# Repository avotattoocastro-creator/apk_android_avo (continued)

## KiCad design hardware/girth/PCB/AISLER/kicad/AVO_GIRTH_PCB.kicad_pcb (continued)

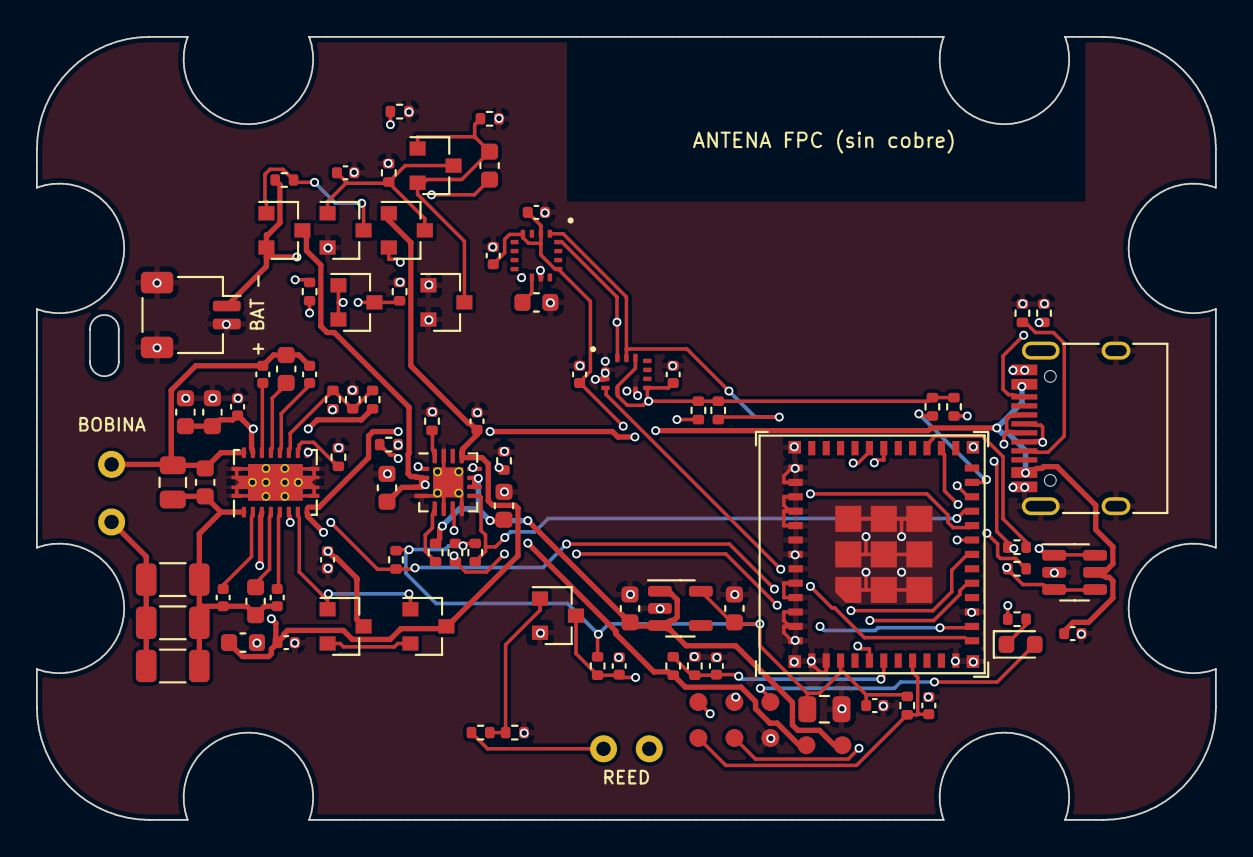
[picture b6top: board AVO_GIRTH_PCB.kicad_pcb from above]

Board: 4 copper layers, 65.5 x 43.5 mm, 98 parts (0 on the bottom side), 55 nets.

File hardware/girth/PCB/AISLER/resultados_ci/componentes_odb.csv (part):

ref,capa,x_mm,y_mm,giro,no_pop,montaje,Value,MPN,Manufacturer,LCSC,paquete
C1,COMP_+_TOP,74.8,-108.4,0.0,False,smt,100n C0G 50V,GRM31C5C1H104JA01L,Murata Electronics,C97946,AVO_C_1206_3216Metric
C2,COMP_+_TOP,74.8,-110.8,0.0,False,smt,100n C0G 50V,GRM31C5C1H104JA01L,Murata Electronics,C97946,AVO_C_1206_3216Metric
C3,COMP_+_TOP,74.8,-113.2,0.0,False,smt,47n C0G 50V,GRM31M5C1H473JA01L,Murata Electronics,C21812,AVO_C_1206_3216Metric
C4,COMP_+_TOP,74.8,-103.0,270.0,False,smt,2n2 C0G 50V,0805CG222J500NT,FH (Guangdong Fenghua Advanced Tech),C51795,AVO_C_0805_2012Metric
C5,COMP_+_TOP,76.6,-103.0,270.0,True,smt,1n C0G 50V,1n C0G 50V,,C1636,AVO_C_0603_1608Metric
C6,COMP_+_TOP,77.6,-109.4,90.0,False,smt,10n 50V,CL05B103KB5NNNC,Samsung Electro-Mechanics,C15195,AVO_C_0402_1005Metric
C7,COMP_+_TOP,79.4,-109.6,90.0,False,smt,470n 25V,CL10B474KA8NNNC,Samsung Electro-Mechanics,C1623,AVO_C_0603_1608Metric
C8,COMP_+_TOP,80.6,-109.4,90.0,False,smt,22n 50V,0402B223K500NT,FH (Guangdong Fenghua Advanced Tech),C1532,AVO_C_0402_1005Metric
C9,COMP_+_TOP,79.8,-97.0,270.0,False,smt,10n 50V,CL05B103KB5NNNC,Samsung Electro-Mechanics,C15195,AVO_C_0402_1005Metric
C10,COMP_+_TOP,81.1,-96.7,270.0,False,smt,470n 25V,CL10B474KA8NNNC,Samsung Electro-Mechanics,C1623,AVO_C_0603_1608Metric
C11,COMP_+_TOP,82.4,-97.0,270.0,False,smt,22n 50V,0402B223K500NT,FH (Guangdong Fenghua Advanced Tech),C1532,AVO_C_0402_1005Metric
C12,COMP_+_TOP,77.0,-99.1,270.0,False,smt,10u 25V,CL10A106MA8NRNC,Samsung Electro-Mechanics,C96446,AVO_C_0603_1608Metric
C13,COMP_+_TOP,75.5,-99.1,270.0,False,smt,10u 25V,CL10A106MA8NRNC,Samsung Electro-Mechanics,C96446,AVO_C_0603_1608Metric
C14,COMP_+_TOP,78.4,-98.8,270.0,False,smt,100n,CL05B104KO5NNNC,Samsung Electro-Mechanics,C1525,AVO_C_0402_1005Metric
C15,COMP_+_TOP,78.7,-111.9,0.0,False,smt,10u 25V,CL10A106MA8NRNC,Samsung Electro-Mechanics,C96446,AVO_C_0603_1608Metric
C16,COMP_+_TOP,81.1,-111.9,0.0,False,smt,100n,CL05B104KO5NNNC,Samsung Electro-Mechanics,C1525,AVO_C_0402_1005Metric
C17,COMP_+_TOP,83.4,-107.3,90.0,False,smt,1u,CL05A105KA5NQNC,Samsung Electro-Mechanics,C52923,AVO_C_0402_1005Metric
C18,COMP_+_TOP,91.7,-99.6,270.0,False,smt,1u,CL05A105KA5NQNC,Samsung Electro-Mechanics,C52923,AVO_C_0402_1005Metric
C19,COMP_+_TOP,93.2,-104.3,270.0,False,smt,10u 25V,CL10A106MA8NRNC,Samsung Electro-Mechanics,C96446,AVO_C_0603_1608Metric
C20,COMP_+_TOP,86.7,-103.3,270.0,False,smt,10u 25V,CL10A106MA8NRNC,Samsung Electro-Mechanics,C96446,AVO_C_0603_1608Metric
C21,COMP_+_TOP,100.2,-110.0,270.0,False,smt,10u 25V,CL10A106MA8NRNC,Samsung Electro-Mechanics,C96446,AVO_C_0603_1608Metric
C22,COMP_+_TOP,106.0,-110.0,270.0,False,smt,10u 25V,CL10A106MA8NRNC,Samsung Electro-Mechanics,C96446,AVO_C_0603_1608Metric
C23,COMP_+_TOP,111.0,-115.6,0.0,False,smt,22u 10V,CL21A226MAQNNNE,Samsung Electro-Mechanics,C45783,AVO_C_0805_2012Metric
C24,COMP_+_TOP,113.8,-115.4,0.0,False,smt,100n,CL05B104KO5NNNC,Samsung Electro-Mechanics,C1525,AVO_C_0402_1005Metric
C25,COMP_+_TOP,116.8,-115.4,270.0,False,smt,1u,CL05A105KA5NQNC,Samsung Electro-Mechanics,C52923,AVO_C_0402_1005Metric
C26,COMP_+_TOP,124.8,-111.4,0.0,False,smt,1u,CL05A105KA5NQNC,Samsung Electro-Mechanics,C52923,AVO_C_0402_1005Metric
C27,COMP_+_TOP,97.4,-97.0,270.0,False,smt,100n,CL05B104KO5NNNC,Samsung Electro-Mechanics,C1525,AVO_C_0402_1005Metric
C28,COMP_+_TOP,102.6,-97.0,270.0,False,smt,100n,CL05B104KO5NNNC,Samsung Electro-Mechanics,C1525,AVO_C_0402_1005Metric
C29,COMP_+_TOP,92.6,-90.4,270.0,False,smt,1u,CL05A105KA5NQNC,Samsung Electro-Mechanics,C52923,AVO_C_0402_1005Metric
C30,COMP_+_TOP,95.0,-93.0,0.0,False,smt,10u 6V3,CL10A106KP8NNNC,Samsung Electro-Mechanics,C19702,AVO_C_0603_1608Metric
C31,COMP_+_TOP,95.0,-88.0,0.0,False,smt,100n,CL05B104KO5NNNC,Samsung Electro-Mechanics,C1525,AVO_C_0402_1005Metric
C33,COMP_+_TOP,99.6,-113.2,270.0,False,smt,10n 50V,CL05B103KB5NNNC,Samsung Electro-Mechanics,C15195,AVO_C_0402_1005Metric
C34,COMP_+_TOP,105.0,-113.2,270.0,False,smt,100n,CL05B104KO5NNNC,Samsung Electro-Mechanics,C1525,AVO_C_0402_1005Metric
C40,COMP_+_TOP,92.4,-85.4,270.0,False,smt,2u2,CL10A225KO8NNNC,Samsung Electro-Mechanics,C23630,AVO_C_0603_1608Metric
C41,COMP_+_TOP,84.4,-85.8,0.0,False,smt,220n,CL05B224KO5NNNC,Samsung Electro-Mechanics,C16772,AVO_C_0402_1005Metric
D1,COMP_+_TOP,121.9,-112.0,0.0,False,smt,LED rojo,KT-0603R,Hubei KENTO Elec,C2286,AVO_LED_0603_1608Metric
D10,COMP_+_TOP,87.8,-89.0,0.0,False,smt,BAV70,BAV70,"Jiangsu Changjing Electronics Technology Co., Ltd.",C68978,AVO_SOT-23
D11,COMP_+_TOP,89.4,-85.4,0.0,False,smt,BAV70,BAV70,"Jiangsu Changjing Electronics Technology Co., Ltd.",C68978,AVO_SOT-23
D12,COMP_+_TOP,85.0,-93.0,0.0,False,smt,BAV70,BAV70,"Jiangsu Changjing Electronics Technology Co., Ltd.",C68978,AVO_SOT-23
D13,COMP_+_TOP,90.0,-93.0,0.0,False,smt,BAV70,BAV70,"Jiangsu Changjing Electronics Technology Co., Ltd.",C68978,AVO_SOT-23
J1,COMP_+_TOP,126.15,-100.0,270.0,False,smt,USB-C 16P,TYPE-C-31-M-12,Korean Hroparts Elec,C165948,AVO_USB_C_Receptacle_HRO_TYPE-C-31-M-12
J2,COMP_+_TOP,75.8,-93.7,90.0,False,smt,BATERÍA 1S,SM02B-SRSS-TB(LF)(SN),JST,C160402,AVO_JST_SH_SM02B-SRSS-TB_1x02-1MP_P1.00mm_Horizontal
L1,COMP_+_TOP,71.4,-105.2,0.0,True,thmt,BOBINA Qi (1),BOBINA Qi (1),,,AVO_WirePad_D1.5_Drill0.8
L2,COMP_+_TOP,71.4,-102.0,0.0,True,thmt,BOBINA Qi (2),BOBINA Qi (2),,,AVO_WirePad_D1.5_Drill0.8
Q1,COMP_+_TOP,84.4,-111.0,0.0,False,smt,AO3401A,AO3401A,Alpha & Omega Semicon,C15127,AVO_SOT-23
Q2,COMP_+_TOP,89.0,-111.0,0.0,False,smt,AO3401A,AO3401A,Alpha & Omega Semicon,C15127,AVO_SOT-23
Q10,COMP_+_TOP,81.0,-89.0,0.0,False,smt,AO3401A,AO3401A,Alpha & Omega Semicon,C15127,AVO_SOT-23
Q11,COMP_+_TOP,84.4,-89.0,0.0,False,smt,AO3400A,AO3400A,Alpha & Omega Semicon,C20917,AVO_SOT-23
Q16,COMP_+_TOP,96.2,-110.4,0.0,False,smt,2N7002,2N7002,"Jiangsu Changjing Electronics Technology Co., Ltd.",C8545,AVO_SOT-23
R1,COMP_+_TOP,83.7,-98.4,270.0,False,smt,330R,0402WGF3300TCE,UNI-ROYAL(Uniroyal Elec),C25104,AVO_R_0402_1005Metric
R2,COMP_+_TOP,84.8,-98.4,270.0,False,smt,200R,0402WGF2000TCE,UNI-ROYAL(Uniroyal Elec),C25087,AVO_R_0402_1005Metric
R3,COMP_+_TOP,85.9,-98.4,270.0,False,smt,20k,0402WGF2002TCE,UNI-ROYAL(Uniroyal Elec),C25765,AVO_R_0402_1005Metric
R4,COMP_+_TOP,87.2,-107.3,270.0,False,smt,100k,0402WGF1003TCE,UNI-ROYAL(Uniroyal Elec),C25741,AVO_R_0402_1005Metric
R6,COMP_+_TOP,89.2,-99.6,270.0,False,smt,3k3,0402WGF3301TCE,UNI-ROYAL(Uniroyal Elec),C25890,AVO_R_0402_1005Metric
R7,COMP_+_TOP,93.2,-101.8,270.0,False,smt,3k3,0402WGF3301TCE,UNI-ROYAL(Uniroyal Elec),C25890,AVO_R_0402_1005Metric
R8,COMP_+_TOP,89.4,-106.9,270.0,False,smt,100k,0402WGF1003TCE,UNI-ROYAL(Uniroyal Elec),C25741,AVO_R_0402_1005Metric
R9,COMP_+_TOP,90.5,-106.9,270.0,False,smt,100k,0402WGF1003TCE,UNI-ROYAL(Uniroyal Elec),C25741,AVO_R_0402_1005Metric
R10,COMP_+_TOP,91.6,-106.9,270.0,False,smt,100k,0402WGF1003TCE,UNI-ROYAL(Uniroyal Elec),C25741,AVO_R_0402_1005Metric
R11,COMP_+_TOP,115.6,-115.4,270.0,False,smt,10k,0402WGF1002TCE,UNI-ROYAL(Uniroyal Elec),C25744,AVO_R_0402_1005Metric
R12,COMP_+_TOP,117.0,-98.8,270.0,False,smt,10k,0402WGF1002TCE,UNI-ROYAL(Uniroyal Elec),C25744,AVO_R_0402_1005Metric
R13,COMP_+_TOP,118.2,-98.8,270.0,False,smt,10k,0402WGF1002TCE,UNI-ROYAL(Uniroyal Elec),C25744,AVO_R_0402_1005Metric
R15,COMP_+_TOP,121.7,-110.6,0.0,False,smt,1k,0402WGF1001TCE,UNI-ROYAL(Uniroyal Elec),C11702,AVO_R_0402_1005Metric
R16,COMP_+_TOP,122.0,-93.6,270.0,False,smt,5k1,0402WGF5101TCE,UNI-ROYAL(Uniroyal Elec),C25905,AVO_R_0402_1005Metric
R17,COMP_+_TOP,123.2,-93.6,270.0,False,smt,5k1,0402WGF5101TCE,UNI-ROYAL(Uniroyal Elec),C25905,AVO_R_0402_1005Metric
R18,COMP_+_TOP,121.7,-106.6,0.0,False,smt,22R,0402WGF220JTCE,UNI-ROYAL(Uniroyal Elec),C25092,AVO_R_0402_1005Metric
R19,COMP_+_TOP,121.7,-107.8,0.0,False,smt,22R,0402WGF220JTCE,UNI-ROYAL(Uniroyal Elec),C25092,AVO_R_0402_1005Metric
R20,COMP_+_TOP,104.0,-99.0,270.0,False,smt,4k7,0402WGF4701TCE,UNI-ROYAL(Uniroyal Elec),C25900,AVO_R_0402_1005Metric
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
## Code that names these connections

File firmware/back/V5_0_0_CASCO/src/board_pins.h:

// AVO CASCO BACK V5 (PROTOTIPO A y REV B: mismos GPIO) — mapa de pines.
// Fuente: hardware/back/V5_CASCO_PROTOTIPO/PCB/fuente/avo_back_v5_pcb.py (diccionario GPIO del módulo U4,
// ESP32-S3-WROOM-1U-N16R8) y la revisión previa a fabricación (claude/AVO_BACK_V5_REVISION_PRE_FABRICACION).
// Los nombres que ya usaba el pecho (PIN_I2C_*, PIN_SD_*, PIN_BOOT_BTN, PIN_PWR_SENSE) se conservan para no tocar
// sus módulos; el resto son nuevos del casco.
#pragma once

#define AVO_CASCO 1

// ---------------------------------------------------------------- I2C: MAX17048 (0x36) + LSM6DSV16X (0x6A)
#define PIN_I2C_SDA 42
#define PIN_I2C_SCL 41
#define I2C_FREQ_HZ 400000
#define I2C_ADDR_MAX17048 0x36
#define I2C_ADDR_LSM6DSV16X 0x6A

// ---------------------------------------------------------------- microSD (SDMMC 4 bits) + interruptor de alimentación
#define PIN_SD_CLK 12
#define PIN_SD_CMD 13
#define PIN_SD_D0 14
#define PIN_SD_D1 15
#define PIN_SD_D2 16
#define PIN_SD_D3 17
#define PIN_SD_PWR_N 21          // Q4 (PMOS): 0 = tarjeta alimentada, 1 = cortada (R40 la deja apagada al arrancar)

// ---------------------------------------------------------------- encendido y entradas
#define PIN_PWR_HOLD 46          // enclavamiento del 3,3 V (pin de arranque: R15 100k a GND). 1 = mantener encendido
#define PIN_TOUCH 11             // salida del TTP223 (activa ALTA mientras se toca). RTC: despierta del sueño profundo
#define PIN_VBUS_DET 18          // 1 = cable del pogo o USB-C conectado (divisor 1k/1k5, RTC)
#define PIN_CHG_PG 38            // BQ24072 PGOOD (colector abierto, activo BAJO): entrada válida
#define PIN_CHG_STAT 39          // BQ24072 CHG (colector abierto, activo BAJO): cargando
#define PIN_BAT_ADC 2            // divisor 1:2 de VBAT (ADC1_CH1); reserva si el MAX17048 no responde
#define PIN_HALL 1               // DRV5032: 0 = casco en la base con imán (RTC)
#define PIN_IMU_INT1 4           // LSM6DSV16X INT1 (RTC)
#define PIN_POGO_AUX 40          // contacto libre del pogo (reservado)

// El pecho leía un botón BOOT (activo BAJO) y la tecla PWR (activa ALTA). En el casco las dos son el táctil:
// controller.cpp lee los dos con AVO_BTN_PRESSED / AVO_PWR_PRESSED.
#define PIN_BOOT_BTN PIN_TOUCH
#define PIN_PWR_SENSE PIN_TOUCH
#define AVO_BTN_PRESSED(level) ((level) == HIGH)
#define AVO_PWR_PRESSED(level) ((level) == HIGH)

// ---------------------------------------------------------------- ZED-F9P (URTK1.2 en el PROTOTIPO A, soldado en la REV B)
#define PIN_ZED_RX 5             // ← TX1 del ZED (330 Ω)
#define PIN_ZED_TX 6             // → RX1 del ZED (1 kΩ). A 0 antes de cortar ZED_EN
#define PIN_ZED_RX2 3            // ← TX2 del ZED (sin usar: pin de arranque, se deja en entrada)
#define PIN_ZED_TX2 8            // → RX2 del ZED (sin usar: a 0 para no alimentar el ZED apagado)
#define PIN_ZED_PPS 7
#define PIN_ZED_RST 9            // RESET_N en colector abierto (1 kΩ). No se usa de forma rutinaria
#define PIN_ZED_EN 10            // EN del RT9080 (3,3 V del ZED y de la antena activa). 1 = encendido

// ---------------------------------------------------------------- anillo LED (SK6812SIDE-A tras el TPS61023)
#define PIN_LED_DIN 47           // datos (330 Ω). A 0 con el anillo apagado
#define PIN_LED_PWR 48           // EN del elevador (4,20 V). 0 = anillo sin alimentación
#define LED_COUNT 8              // PROTOTIPO A: 8 (REV B: 7; el octavo dato se pierde sin daño)
#define LED_MAX_BRIGHT 77        // 30 % de 255: límite de la revisión (F1 1,5 A y calor)

// ---------------------------------------------------------------- enlace por cable con la espalda (no existe en el casco)
#define PIN_LINK_TX -1
#define PIN_LINK_RX -1

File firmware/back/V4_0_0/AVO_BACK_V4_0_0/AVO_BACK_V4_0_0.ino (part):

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 *     desde una tarea propia (el bucle GNSS/RTCM nunca espera a la tarjeta). El fichero se vacía cada segundo: al
 *     quitar la cápsula se corta la corriente sin aviso y se pierde como mucho el último segundo.
 *   - PPS del ZED en GPIO4: marca de tiempo por interrupción (estadística de periodo/jitter en el monitor).
 *   - Batería por ADC (GPIO2, divisor 1:2).
 * Órdenes por el puerto USB (115200): PAIR · DORMIR · SD · ESTADO
 * Build: ../build_back_v4.sh (arduino-cli, núcleo esp32 3.3.12, ESP32S3 Dev Module, 8 MB, USB CDC al arrancar).
 * NO VERIFICADO EN HARDWARE: la placa V4 no se ha fabricado.
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}

static bool sd_start() {
  pinMode(PIN_SD_PWR_N, OUTPUT);
  digitalWrite(PIN_SD_PWR_N, LOW);           // card powered
  delay(20);
  if (!SD_MMC.setPins(PIN_SD_CLK, PIN_SD_CMD, PIN_SD_D0, PIN_SD_D1, PIN_SD_D2, PIN_SD_D3)) return false;
  if (!SD_MMC.begin("/sdcard", false, false, SDMMC_FREQ_DEFAULT, 2)) {
    digitalWrite(PIN_SD_PWR_N, HIGH);
    return false;
  }
  uint32_t n = prefs.getUInt("logn", 0) + 1;
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static void sd_stop() {
  s_sd_ok = false;
  SD_MMC.end();
  pinMode(PIN_SD_PWR_N, OUTPUT);
  digitalWrite(PIN_SD_PWR_N, HIGH);          // card off
}

static void sd_task(void*) {
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static BackCore* core = nullptr;

// ------------------------------------------------------------------ helpers
static bool usb_power() { return digitalRead(PIN_CHG_PG) == LOW; }     // workshop USB-C present
static bool charging() { return digitalRead(PIN_CHG_STAT) == LOW; }
static void led(bool on) { digitalWrite(PIN_LED, on ? LOW : HIGH); }

static uint16_t read_battery_mv() {
  uint32_t acc = 0;
  for (int i = 0; i < 16; i++) acc += analogReadMilliVolts(PIN_BAT_ADC);
  return battery_mv_from_adc(acc / 16);
}

static void zed_lines_safe() {               // unpowered ZED must not be fed through its RX lines
  pinMode(PIN_S3_TX1, OUTPUT); digitalWrite(PIN_S3_TX1, LOW);
  pinMode(PIN_S3_TX2, OUTPUT); digitalWrite(PIN_S3_TX2, LOW);
  pinMode(PIN_ZED_TX1, INPUT); pinMode(PIN_ZED_TX2, INPUT);
  pinMode(PIN_ZED_RST, INPUT);
}

static void zed_power_on() {
  gpio_hold_dis((gpio_num_t)PIN_ZED_EN);
  pinMode(PIN_ZED_EN, OUTPUT);
  digitalWrite(PIN_ZED_EN, HIGH);            // RT9080 on (its soft start; the ESP32 3V3 is a separate regulator)
  delay(50);
  ZED.setRxBufferSize(8192);
  ZED.setTxBufferSize(4096);
  ZED.begin(38400, SERIAL_8N1, PIN_ZED_TX2, PIN_S3_TX2);   // RX, TX
  ZED.setRxTimeout(1);
  s_zed_on = true;
  pinMode(PIN_ZED_PPS, INPUT);
  attachInterrupt(digitalPinToInterrupt(PIN_ZED_PPS), on_pps, RISING);
  Serial.println("[AVO ESPALDA V4] ZED alimentado (RT9080, EN = GPIO10)");
}

static void zed_power_off() {
  if (s_zed_on) { detachInterrupt(digitalPinToInterrupt(PIN_ZED_PPS)); ZED.end(); s_zed_on = false; }
  s_zed_pending = false;
  zed_lines_safe();
  pinMode(PIN_ZED_EN, OUTPUT);
  digitalWrite(PIN_ZED_EN, LOW);             // 0 V on the receiver and the active antenna
}

static void radio_on() {
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  radio_off();
  if (s_sd_ok) { delay(300); sd_stop(); }
  zed_power_off();
  gpio_hold_en((gpio_num_t)PIN_ZED_EN);
  gpio_hold_en((gpio_num_t)PIN_S3_TX1);
  gpio_hold_en((gpio_num_t)PIN_S3_TX2);
  pinMode(PIN_SD_PWR_N, OUTPUT); digitalWrite(PIN_SD_PWR_N, HIGH); gpio_hold_en((gpio_num_t)PIN_SD_PWR_N);
  led(false); gpio_hold_en((gpio_num_t)PIN_LED);
#if SOC_GPIO_SUPPORT_HOLD_IO_IN_DSLP && !SOC_GPIO_SUPPORT_HOLD_SINGLE_IO_IN_DSLP
  gpio_deep_sleep_hold_en();
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                (unsigned)s_vbat_mv, usb_power() ? (charging() ? "cargando por USB" : "sin carga (sin bateria puenteada o llena)") : "");
  Serial.printf("  MICROSD: %s %s escritos=%lu B perdidos=%lu B errores=%lu (deteccion=%s)\n", s_sd_ok ? "GRABANDO" : "sin tarjeta",
                s_sd_name, (unsigned long)s_sd_bytes, (unsigned long)s_log.dropped(), (unsigned long)s_sd_errors,
                digitalRead(PIN_SD_CD) == (s_sd_present_level ? HIGH : LOW) ? "tarjeta" : "?");
  Serial.printf("  AHORRO: CPU %lu MHz | potencia radio %d dBm%s\n", (unsigned long)getCpuFrequencyMhz(), (int)s_txp.dbm(),
                s_txp.level() == TxPowerPolicy::kLevels - 1 ? " (maxima)" : "");
  {
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#if SOC_GPIO_SUPPORT_HOLD_IO_IN_DSLP && !SOC_GPIO_SUPPORT_HOLD_SINGLE_IO_IN_DSLP
  gpio_deep_sleep_hold_dis();
#endif
  for (int p : {PIN_ZED_EN, PIN_S3_TX1, PIN_S3_TX2, PIN_SD_PWR_N, PIN_LED}) gpio_hold_dis((gpio_num_t)p);
  zed_power_off();                           // ZED at 0 V until the 3V3 rail and the ESP32 are up
  pinMode(PIN_SD_PWR_N, OUTPUT); digitalWrite(PIN_SD_PWR_N, HIGH);
  pinMode(PIN_LED, OUTPUT); led(true);
  pinMode(PIN_CHG_PG, INPUT); pinMode(PIN_CHG_STAT, INPUT);
  pinMode(PIN_SD_CD, INPUT);
  analogSetPinAttenuation(PIN_BAT_ADC, ADC_11db);
  setCpuFrequencyMhz(CPU_MHZ);
  delay(300);
  // REV B: having power means the capsule is on the vest support (or on the workshop USB): everything starts.
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  s_vbat_mv = read_battery_mv();
  core->set_battery_mv(s_vbat_mv);

  s_sd_present_level = digitalRead(PIN_SD_CD);   // level seen at boot with a card is taken as "present"
  if (sd_start()) {
    s_sd_ok = true;
    xTaskCreatePinnedToCore(sd_task, "avo_sd", 6144, nullptr, 1, nullptr, 0);
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
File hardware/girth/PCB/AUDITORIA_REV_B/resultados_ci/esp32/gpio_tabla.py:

"""Tabla GPIO firmware ↔ esquema/placa (fase 5). Fuentes independientes:
 - firmware: firmware/girth/V0_3_0_C3/AVO_GIRTH_V0_3_0/girth_board.h (PIN_*)
 - módulo: símbolo oficial de Espressif (ESP32-C3-MINI-1, número de pin → GPIO)
 - placa: red de cada pad de U4 en la placa entregada (out/C3/KiCad/AVO_GIRTH_PCB.kicad_pcb)
Uso: python3 gpio_tabla.py [ruta_simbolo_espressif]  → gpio_tabla.md + gpio_tabla.json"""
import json
import os
import re
import sys

H = os.path.dirname(os.path.abspath(__file__))
ROOT = os.path.join(H, "..", "..", "..", "..", "..")
SYM = sys.argv[1] if len(sys.argv) > 1 else os.path.join(H, "ESP32-C3-MINI-1_simbolo_espressif.kicad_sym.txt")
board_h = open(os.path.join(ROOT, "firmware/girth/V0_3_0_C3/AVO_GIRTH_V0_3_0/girth_board.h")).read()
fw = {name: int(v) for name, v in re.findall(r"static const int (PIN_\w+)\s*=\s*(\d+);", board_h)}
# símbolo: pines del ESP32-C3-MINI-1 (el -1U usa el mismo)
s = open(SYM).read()
i = s.find('(symbol "ESP32-C3-MINI-1"'); j = s.find('\n\t(symbol "', i + 10)
blk = s[i:j]
pin_gpio = {}
for name, num in re.findall(r'\(pin \w+ \w+.*?\(name "([^"]*)".*?\(number "([^"]*)"', blk, re.S):
    m = re.match(r"GPIO(\d+)", name)
    if m:
        pin_gpio[num] = int(m.group(1))
gpio_pin = {g: p for p, g in pin_gpio.items()}
# placa: red de cada pad de U4
pcb = open(os.path.join(ROOT, "hardware/girth/PCB/out/C3/KiCad/AVO_GIRTH_PCB.kicad_pcb")).read()
u4 = [b for b in pcb.split("\n\t(footprint ")[1:] if re.search(r'"Reference" "U4"', b)][0]
pad_net = {}
for m in re.finditer(r'\(pad "(\d+)".*?\(net \d+ "([^"]*)"\)', u4, re.S):
    pad_net.setdefault(m.group(1), m.group(2))
EXPECT = {"PIN_IMU_INT": "IMU_INT", "PIN_REED": "REED", "PIN_SCL": "I2C_SCL", "PIN_BAT_ADC": "BAT_ADC",
          "PIN_CHG_PG": "CHG_PG", "PIN_PWR_HOLD": "PWR_HOLD", "PIN_SDA": "I2C_SDA", "PIN_CHG_STAT": "CHG_STAT",
          "PIN_LED": "LED", "PIN_BOOT": "BOOT", "PIN_QI_CHG": "QI_CHG"}
rows, bad = [], 0
for name, g in sorted(fw.items(), key=lambda kv: kv[1]):
    pin = gpio_pin.get(g)
    net = pad_net.get(pin)
    ok = net == EXPECT.get(name)
    bad += not ok
    rows.append(dict(firmware=name, gpio=g, pin_modulo=pin, red_placa=net, esperada=EXPECT.get(name), ok=ok))
for g, fixed in ((18, "USB_DM"), (19, "USB_DP"), (20, "U0RX"), (21, "U0TX")):
    pin = gpio_pin.get(g); net = pad_net.get(pin); ok = net == fixed; bad += not ok
    rows.append(dict(firmware="(núcleo: USB / UART0)", gpio=g, pin_modulo=pin, red_placa=net, esperada=fixed, ok=ok))
used = {r["gpio"] for r in rows}
free = sorted(set(pin_gpio.values()) - used)
L = ["| Nombre en el firmware | GPIO | Pin del módulo | Red en la placa | Esperada | Coincide |", "|---|---|---|---|---|---|"]
for r in rows:
    L.append("| %s | %d | %s | %s | %s | %s |" % (r["firmware"], r["gpio"], r["pin_modulo"], r["red_placa"], r["esperada"],
                                              "sí" if r["ok"] else "**NO**"))
L.append("")
L.append("GPIO del módulo sin usar: %s · discrepancias: %d" % (free or "ninguno", bad))
open(os.path.join(H, "gpio_tabla.md"), "w").write("\n".join(L) + "\n")
json.dump(dict(filas=rows, libres=free, discrepancias=bad), open(os.path.join(H, "gpio_tabla.json"), "w"), indent=1)
print("\n".join(L))
sys.exit(1 if bad else 0)

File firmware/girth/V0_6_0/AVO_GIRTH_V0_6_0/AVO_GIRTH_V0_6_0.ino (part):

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
// ---------------------------------------------------------------- pins (PCB REV D, ESP32-C6-MINI-1U; same numbers as the XIAO where shared)
static const int PIN_RING_DIN = 15;   // light ring data (4 × SK6812SIDE-A); was the green LED
static const int PIN_RING_EN = 18;    // light ring power (Q2 → Q1): HIGH = VLED on
static const int PIN_CHG = 8;         // BQ24072 CHG (open drain, pull-up R10): LOW = charging
static girth::Ring ring;
static const int PIN_BOOT = 9;        // BOOT button, active low
// (no RF switch on the REV D: GPIO3 = ADS1292 DRDY, GPIO14 = ADS1292 DIN)
static const int PIN_BAT = 5;         // MTDI / A? : battery divider
static const int PIN_DET = 6;         // MTCK (LP GPIO): mount detection (pogo contact 3, bridged to GND on the mount)
static const girth::ImuPins IMU_PINS = {23, 16, 2, 17, 22};         // sda, scl, int1, int2, mag_int
static const girth::EcgPins ECG_PINS = {0, 1, 7, 14, 3, 4, 21};     // cs, sck, miso (DOUT), mosi (DIN), drdy, pwdn/reset, start

static const uint32_t IMU_INTERVAL_US = 10000;   // 100 Hz
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  esp_now_deinit();
  esp_wifi_stop();
  ring.show({0, 0, 0});
  rtc_gpio_pullup_en((gpio_num_t)PIN_DET);
  rtc_gpio_pulldown_dis((gpio_num_t)PIN_DET);
  esp_deep_sleep_enable_gpio_wakeup(1ULL << PIN_DET, ESP_GPIO_WAKEUP_GPIO_LOW);
  esp_deep_sleep_start();
}

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                (unsigned long)s_imu_discard_nolink, s_bat_mv ? "" : "no medida");
  if (s_bat_mv) Serial.printf("%u mV (~%u %%, estimado)", s_bat_mv, s_bat_pct);
  Serial.printf(" [pin GPIO5 %u mV, divisor %.2f sin verificar] | soporte %s | reposo %s\n", s_bat_pin_mv, s_bat_ratio,
                digitalRead(PIN_DET) == LOW ? "PUESTO" : "fuera/sin conectar", s_sleep_enabled ? "on" : "off");
}

// ---------------------------------------------------------------- setup / loop
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  pinMode(PIN_CHG, INPUT);
  pinMode(PIN_BOOT, INPUT_PULLUP);
  gpio_hold_dis((gpio_num_t)ECG_PINS.reset);         // after deep sleep the ECG power-down was held
  if (rtc_gpio_is_valid_gpio((gpio_num_t)PIN_DET)) rtc_gpio_deinit((gpio_num_t)PIN_DET);
  pinMode(PIN_DET, INPUT_PULLUP);
  analogReadResolution(12);
  analogSetPinAttenuation(PIN_BAT, ADC_11db);

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
  // idle mode: out of the mount for 30 s -> deep sleep (only if enabled)
  static uint32_t off_mount_since = 0;
  if (s_sleep_enabled && digitalRead(PIN_DET) == HIGH) {
    if (!off_mount_since) off_mount_since = now | 1;
    else if (now - off_mount_since > 30000) go_to_sleep();
  } else off_mount_since = 0;
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  {
    girth::EcgStatus es = ecg.status();
    girth::RingState rs{linked(), imu_running(), es.state == girth::EcgState::RUNNING,
                        es.state == girth::EcgState::RUNNING && es.leads_off, digitalRead(PIN_DET) == LOW,
                        digitalRead(PIN_CHG) == LOW, s_bat_pct};
    ring.show(girth::ring_colour(rs, now));
  }
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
